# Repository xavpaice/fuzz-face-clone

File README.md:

Fuzz Face Clone
===============

Copyright (c) 2014 Xav Paice

Version 0.1 - initial prototype

Based on the original Fuzz Face overdrive pedal.
I have made some modifications, mainly just using silicon transistors
plus some values to suit the differences.  Also this version runs on
12V for the PSU since that's what I mostly have on the bench.

This is an Open Hardware project. For details about OSHW, go to:
http://freedomdefined.org/OSHW

All documentation and drawings are covered by Creative Commons Attribution
4.0 International License.

<br /><span xmlns:dct="http://purl.org/dc/terms/" property="dct:title">Hybrid Headphone Amp</span> by <a xmlns:cc="http://creativecommons.org/ns#" href="https://github.com/xavpaice/hybridheadphoneamp" property="cc:attributionName" rel="cc:attributionURL">Xav Paice</a> is licensed under a <a rel="license" href="http://creativecommons.org/licenses/by/4.0/">Creative Commons Attribution 4.0 International License</a>.<br />Based on a work at <a xmlns:dct="http://purl.org/dc/terms/" href="https://github.com/xavpaice/hybridheadphoneamp" rel="dct:source">https://github.com/xavpaice/hybridheadphoneamp</a>.

The schematic and PCB are all drawn with Kicad (http://www.kicad-pcb.org/).

TODO list:
----------

Hacking:
--------
* Please do.
* Please submit pull requests, I'd love some help

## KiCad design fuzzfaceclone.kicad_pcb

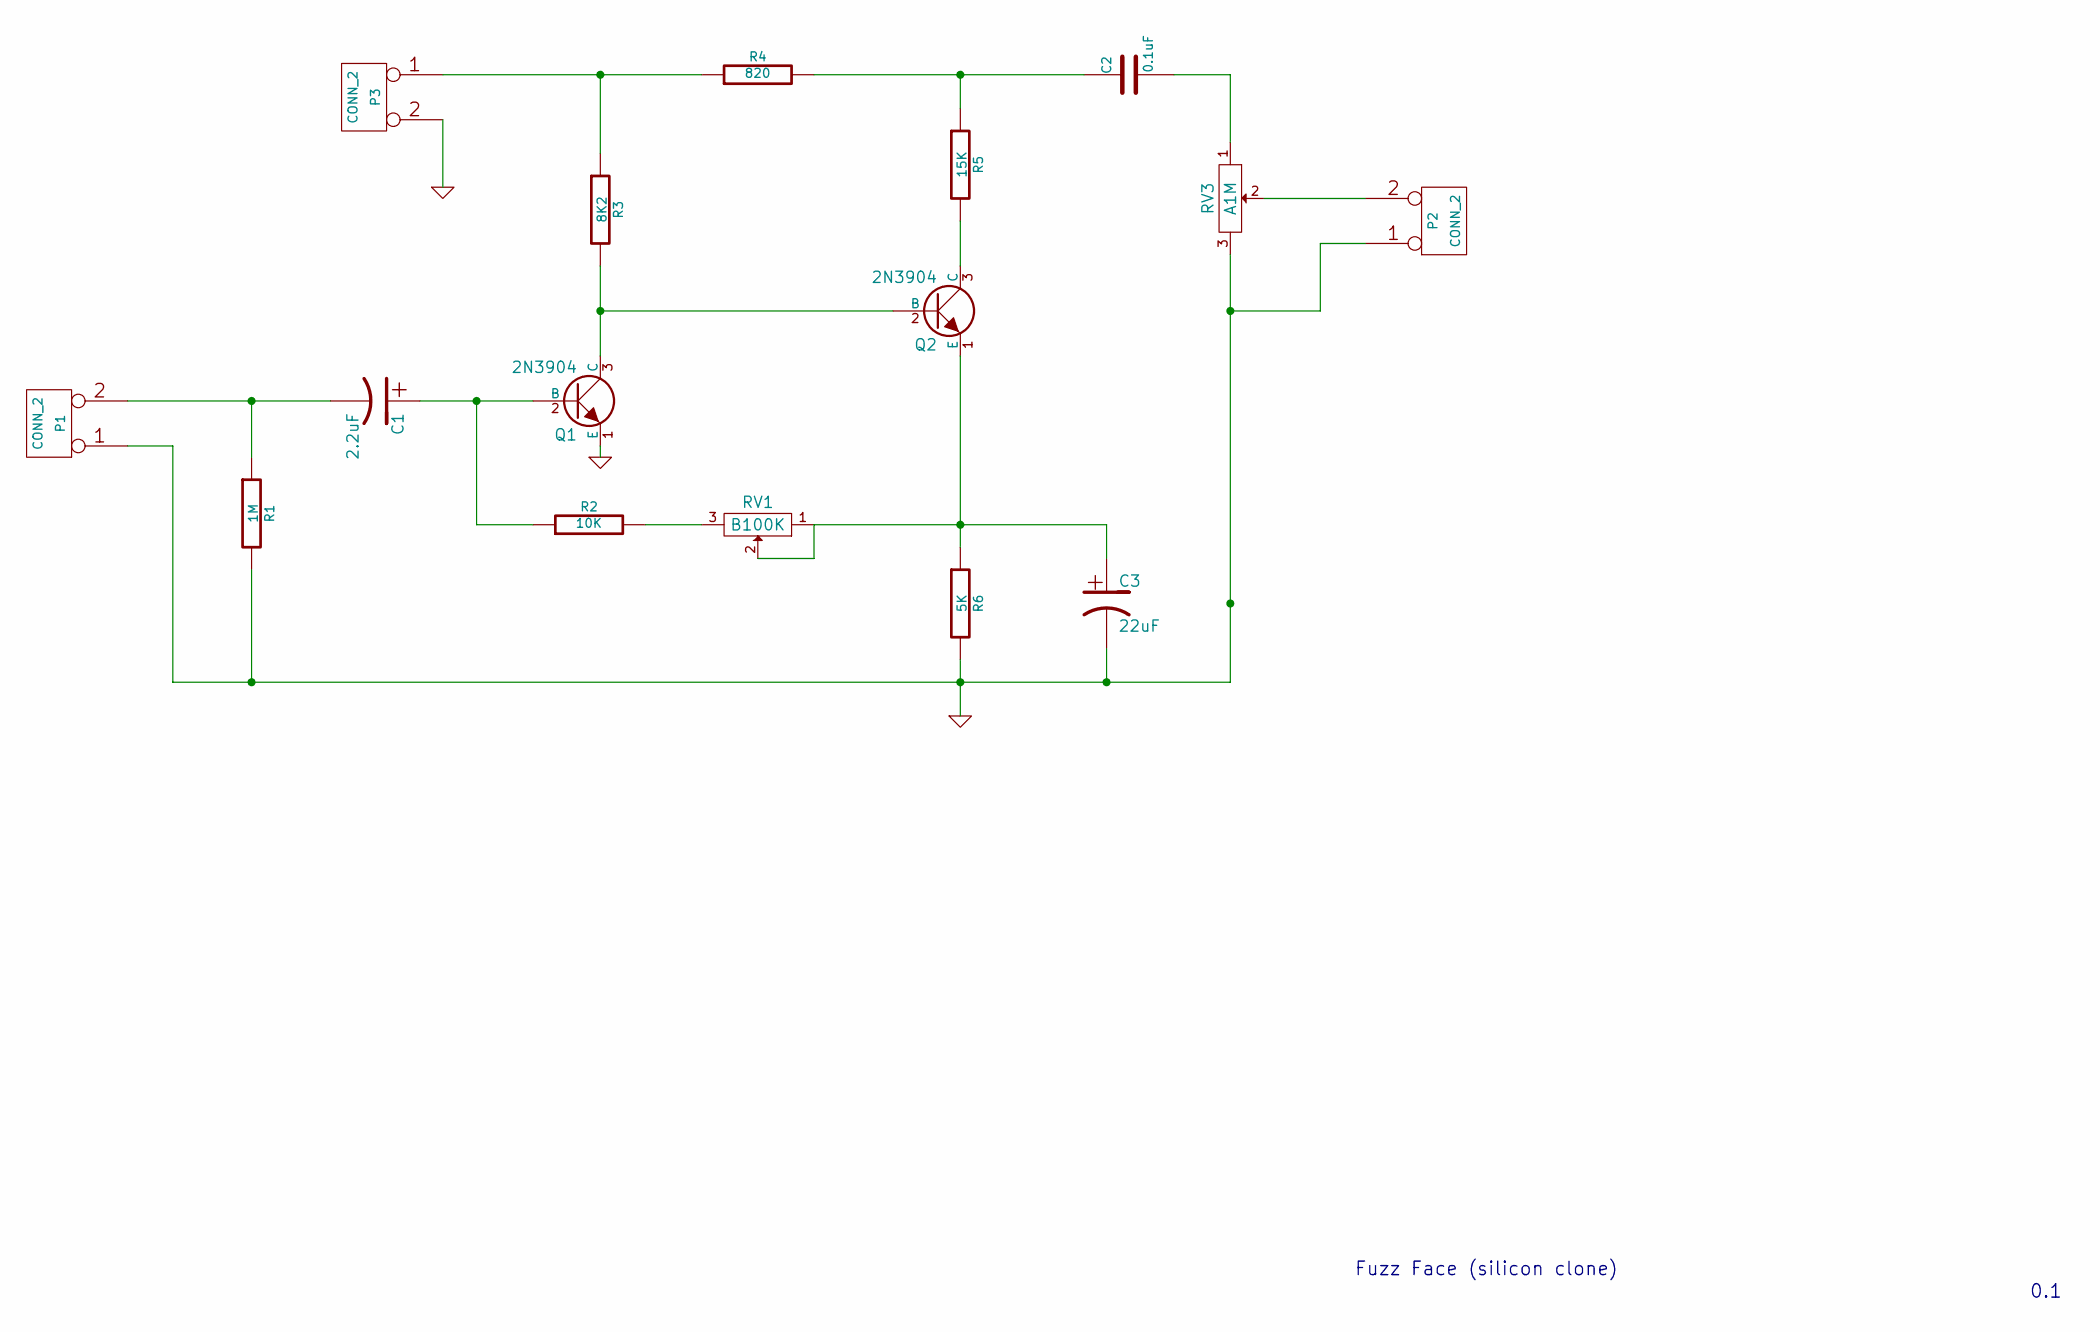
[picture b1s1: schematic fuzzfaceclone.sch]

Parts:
C1: 2.2uF; Capacitor8x13RM3.8
C2: 0.1uF; C2
C3: 22uF; Capacitor8x21RM3.8
P1, P2, P3: CONN_2; SIL-2
Q1, Q2: 2N3904; TO92-EBC
R1: 1M; Resistor_Horizontal_RM10mm
R2: 10K; Resistor_Horizontal_RM10mm
R3: 8K2; Resistor_Horizontal_RM10mm
R4: 820; Resistor_Horizontal_RM10mm
R5: 15K; Resistor_Horizontal_RM10mm
R6: 5K; Resistor_Horizontal_RM10mm
RV1: B100K; SIL-3
RV3: A1M; SIL-3

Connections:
GND: C3.2, P1.1, P2.1, P3.2 (PM), Q1.1 (E), R1.2, R6.2, RV3.3
unnamed: C1.1, Q1.2 (B), R2.1
unnamed: C1.2, P1.2 (PM), R1.1
unnamed: C2.1, R4.2, R5.1
unnamed: C2.2, RV3.1
unnamed: C3.1, Q2.1 (E), R6.1, RV1.1, RV1.2
unnamed: P2.2 (PM), RV3.2
unnamed: P3.1, R3.1, R4.1
unnamed: Q1.3 (C), Q2.2 (B), R3.2
unnamed: Q2.3 (C), R5.2
unnamed: R2.2, RV1.3

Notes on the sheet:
0.1
Fuzz Face (silicon clone)

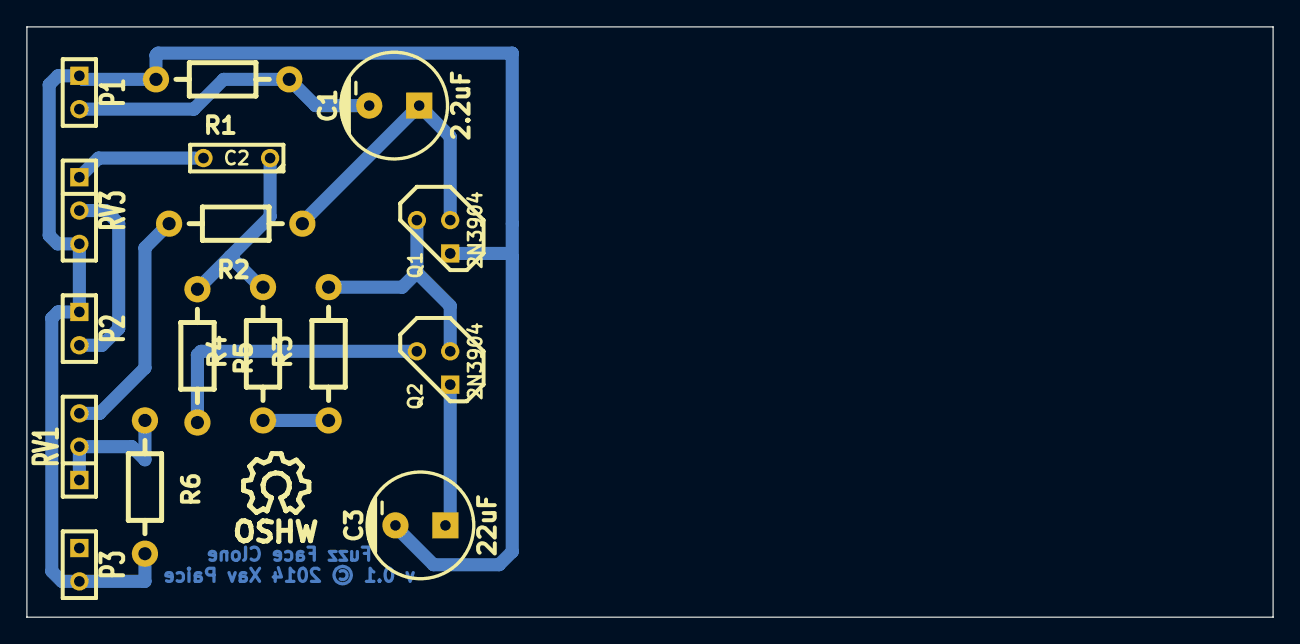
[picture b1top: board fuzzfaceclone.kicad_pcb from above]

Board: 2 copper layers, 95.0 x 45.0 mm, 17 parts (0 on the bottom side), 11 nets.

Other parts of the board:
SYM: Symbol_OSHW-Logo_SilkScreen_07Jul2012; Symbol_OSHW-Logo_SilkScreen

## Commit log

2014-06-22 First draft, not yet verified

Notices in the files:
fuzzfaceclone.kicad_pcb:
v 0.1 © 2014 Xav Paice
